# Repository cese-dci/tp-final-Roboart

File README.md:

## Trabajo práctico final de la asignatura DCI ##
Este repositorio contiene el trabajo práctico final para la asignatura de Diseño de Circuitos Impresos de la carrera de posgrado de FIUBA.

* Autor: Osvaldo Rodriguez
* Título corto del trabajo:  I2S Stereo Decoder - UDA1334A
* Descripción:  Modulo conversor de audio DAC  para protocolo I2S.

## Licencia de este trabajo ##
Licencia Hardware: Creative Commons 4.0 International.

## Estructura del TP FINAL ##

Se propone y se pide utilizar la siguiente estructura.

* doc: Toda la información sobre el circuito, principalmente de autoría o procesamiento propio. Por ejemplo:
  * Notas de ingeniería propias.
  * Notas de aplicación propias.
  * Estudios previos, estado del arte, resumen de las investigaciones.
  * Notas con cálculos.
  * Dibujos adicionales.
  * Fotos de los prototipos.
  * Presupuestos, cotizaciones.
* info: Toda la iformación recolectada, principalmente de terceros, como por ejemplo:
  * Hojas de datos.
  * Notas de aplicación.
  * Info de productos comerciales.
  * Info en internet.
* pcb: Archivos de diseño esquemático y pcb.

Dependiendo la magnitud del proyecto, tendremos más o menos información en estos directorios. 
Revisar los README.md en cada directorio para conocer las pautas de cada uno para este TP.

NOTA: El alumno puede y debe borrar de este archivo todo lo que considere necesario, por ejemplo las aclaraciones del docente y esta misma nota.

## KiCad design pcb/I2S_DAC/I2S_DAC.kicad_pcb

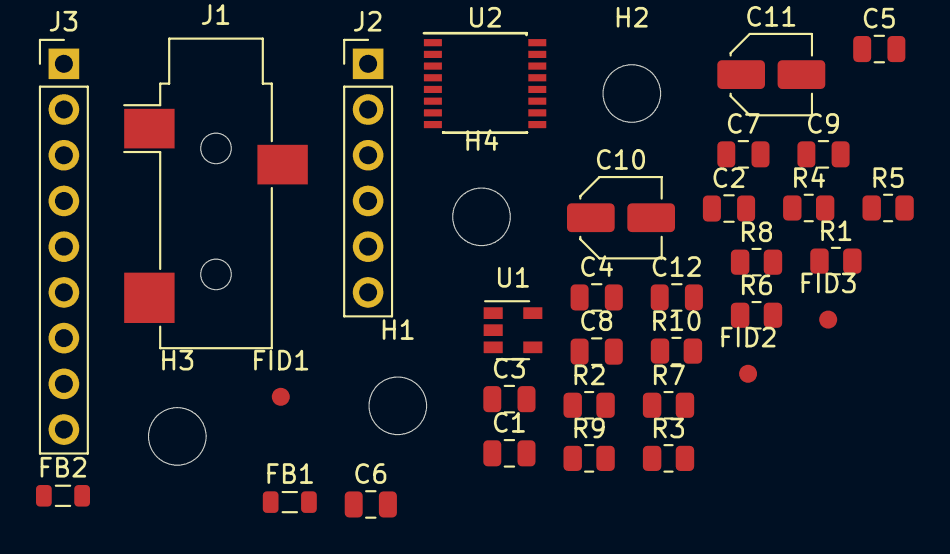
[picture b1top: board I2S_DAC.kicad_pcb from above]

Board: 2 copper layers, 36 parts (0 on the bottom side), 21 nets, no tracks yet.

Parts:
C1, C2, C3, C5, C12: 10uF; C_0805_2012Metric
C4, C6, C9: 0.1uF; C_0805_2012Metric
C7, C8: 0.01uF; C_0805_2012Metric
C10, C11: 47uF; C_Elec_4x5.4
FB1, FB2: Ferrite; L_0805_2012Metric
FID1, FID2, FID3: Fiducial; Fiducial_1mm_Mask2mm
H1, H2, H3, H4: MountingHole; MountingHole_3.2mm_M3
J1: AudioPlug3; Jack_3.5mm_CUI_SJ-3523-SMT_Horizontal
J2: Conn_01x06; PinHeader_1x06_P2.54mm_Vertical
J3: Conn_01x09; PinHeader_1x09_P2.54mm_Vertical
R1, R2, R3, R4, R5, R6: R; R_0805_2012Metric
R7, R9: 100; R_0805_2012Metric
R8, R10: 220K; R_0805_2012Metric
U1: MIC5225-3.3YM5; SOT-23-5
U2: UDA1334ATS; SSOP-16_4.4x5.2mm_P0.65mm

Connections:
+3V3: C2.1, C3.2, C4.1, FB2.2, J3.2, U1.5, U2.4
/BCK_IN: J3.6, U2.1
/CLKOUT: J2.6, R3.1, U2.9
/DATA_IN: J3.5, U2.3
/MUTE: J2.3, R4.1, U2.8
/OUT_L: C8.1, J1.S, J3.7, R7.1
/PLL_IN: J2.5, R1.1, U2.10
/SFOR_0: J2.4, R5.1, U2.11
/SFOR_1: J2.2, R6.1, U2.7
/SYSCLK_IN: J2.1, R2.1, U2.6
/WS_IN: J3.4, U2.2
GNDA: C5.1, C6.1, C7.1, C8.2, C9.2, C12.2, FB1.1, J1.T, J3.8, R8.1, R10.2, U2.15
GNDD: C1.2, C2.2, C3.1, C4.2, FB1.2, J3.3, R1.2, R2.2, R3.2, R4.2, R5.2, R6.2, U1.2, U2.5
unnamed: C5.2, C6.2, FB2.1, U2.13
unnamed: C7.2, J1.R, R9.1
unnamed: C10.1, U2.14
unnamed: C10.2, R7.2, R8.2
unnamed: C11.1, U2.16
unnamed: C11.2, R9.2, R10.1
unnamed: C9.1, C12.1, U2.12
VDD: C1.1, J3.1, U1.1, U1.3

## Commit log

2021-09-22 Primer commit: Creacion esquematico - documentacion detalle y hojas de datos
2021-09-22 Create LICENSE
    Add Licencse
2021-09-22 edicion de licencia en SCH
2021-09-22 Commit sin importancia: sólo test de commit
2021-09-23 Se corrige error del esquemático - ERC
2021-10-14 Archivos finales presentacion 14-10-2021
